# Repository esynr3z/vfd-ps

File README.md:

# Power supply for VFD

## Features

Main parts of the VFD power supply: inverting buck-boost converter on TPS54360 (supposed to use with ICs like PT6311 and etc) and filament driver on LM4871.

Inverting converter:

* Input voltage: 5V
* Output negative voltage: -15V to -30V
* Output current: 250mA @ 5V in

Filament driver:

* Input voltage: 5V
* Output voltage: 5 to 0 (dummy resistors to regulate)
* Output power: 2W @ 5V in

## Board

Schematic and pcb layout created in KiCad 6 Nightly Build (compatible with KiCad 5).

## Notes

* ```misc``` folder contains some calculation and simulation sheets for several IC to get negative voltages

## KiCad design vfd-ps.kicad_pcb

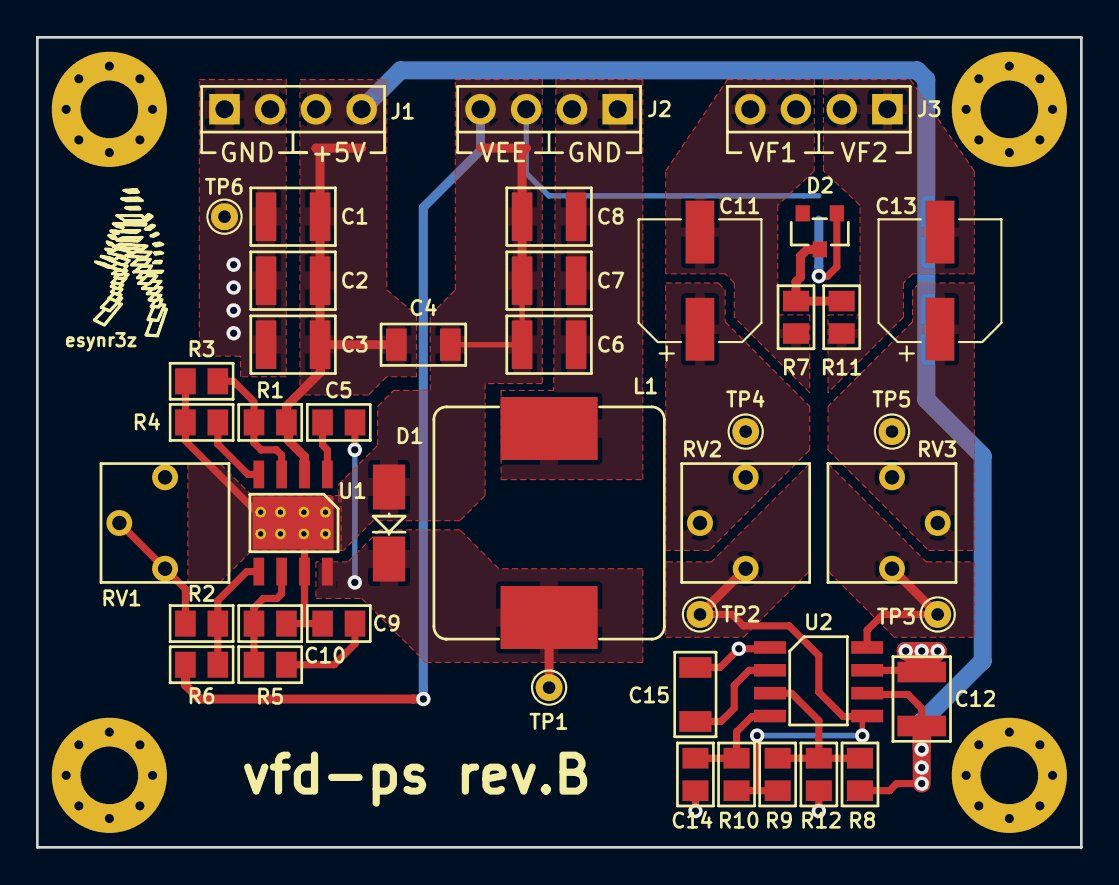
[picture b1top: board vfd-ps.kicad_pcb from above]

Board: 2 copper layers, 58.0 x 45.0 mm, 45 parts (1 on the bottom side), 22 nets.

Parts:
C1, C2, C3, C12: 22u; C_1210
C4, C15: 1u; C_1206
C5: 100n; C_0805
C6, C7, C8: 4.7u; C_1210
C9: 220n; C_0805
C10: 1.8n; C_0805
C11, C13: 22u; CP_Elec_6.3x7.7
C14: 10n; C_0805
D1: MBRA340; SMA
D2: BZX84C4V7; SOT-23
J1, J2, J3: Conn_01x04; PinHeader_1x04_P2.54mm_Vertical
JP1: SolderJumper_2_Bridged; SolderJumper-2_P1.3mm_Bridged2Bar_RoundedPad1.0x1.5mm
L1: 33u; Sumida_CDRH127
R1, R3: dnf; R_0805
R2: 36k; R_0805
R4: 220k; R_0805
R5: 6.8k; R_0805
R6, R10: 2.2k; R_0805
R7, R11: 100; R_0805
R8, R9, R12: 10k; R_0805
RV1: 50k; Bourns_3362P
RV2, RV3: 50; Bourns_3362P
TP1, TP2, TP3, TP4, TP5, TP6: TestPoint; TestPoint_THTPad_D1.5mm_Drill0.7mm
U1: TPS54360DDA; TI_SO-PowerPAD-8_ThermalVias
U2: LM4871; SOIC-8_3.9x4.9mm_P1.27mm

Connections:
+5V: C1.1, C2.1, C3.1, C4.1, C12.1, J1.3, J1.4, R1.1, R8.2, U1.2, U2.6
GND: C1.2, C2.2, C3.2, C6.1, C7.1, C8.1, C12.2, C14.2, C15.2, J1.1, J1.2, J2.1, J2.2, L1.2, R12.2, RV1.1, TP6.1, U2.1, U2.7
GNDPAD: C4.2, C6.2, C7.2, C8.2, C9.2, C10.2, D1.2, J2.3, J2.4, JP1.1, R3.2, R4.2, R6.2, U1.7, U1.9
unnamed: C5.1, U1.1
unnamed: C5.2, D1.1, L1.1, TP1.1, U1.8
unnamed: C9.1, R5.2
unnamed: C10.1, R5.1, U1.6
unnamed: C11.1, RV2.1, RV2.2, TP4.1
unnamed: C13.1, RV3.2, RV3.3, TP5.1
unnamed: C14.1, R10.1, U2.4
unnamed: C15.1, U2.2
unnamed: D2.1, JP1.2
unnamed: D2.3, R7.2, R11.1
unnamed: R1.2, R3.1, U1.3
unnamed: R2.1, RV1.2, RV1.3
unnamed: R2.2, R6.1, U1.5
unnamed: R4.1, U1.4
unnamed: R9.2, R10.2, RV2.3, TP2.1, U2.5
unnamed: R8.1, R9.1, R12.1, U2.3
unnamed: RV3.1, TP3.1, U2.8
VF1: C11.2, J3.3, J3.4, R7.1
VF2: C13.2, J3.1, J3.2, R11.2

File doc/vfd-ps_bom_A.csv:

Component,Description,Part,References,Value,Footprint,Quantity Per PCB,Datasheet,Rating
1,,Device_C,C10,1.8n,C_0805,1,~,
2,,Device_C,C5,100n,C_0805,1,~,
3,,Device_C,C14,10n,C_0805,1,~,
4,,Device_C,C4 C15,1u,C_1206,2,~,50V X7R
5,,Device_C,C9,220n,C_0805,1,~,
6,,Device_C,C1 C2 C3 C12,22u,C_1210,4,~,16V X5R
7,,Device_CP,C11 C13,22u,CP_Elec_6.3x7.7,2,~,50V
8,,Device_C,C6 C7 C8,4.7u,C_1210,3,~,50V X7R
9,,esynr3z_DiodeZener_BZX84C4V7,D2,BZX84C4V7,SOT-23,1,https://www.onsemi.com/pub/Collateral/BZX84C2V4LT1-D.PDF,
10,,esynr3z_DiodeSchottky_MBRA340,D1,MBRA340,SMA,1,https://www.onsemi.com/pub/Collateral/MBRA340T3-D.PDF,
11,,Connector_Generic_Conn_01x04,J1 J2 J3,Conn_01x04,PinHeader_1x04_P2.54mm_Vertical,3,~,
12,,Device_L_Core_Iron,L1,33u,Sumida_CDRH127,1,~,
13,,Device_R,R7 R11,100,R_0805,2,~,
14,,Device_R,R8 R9 R12,10k,R_0805,3,~,
15,,Device_R,R2,16k,R_0805,1,~,
16,,Device_R,R6,1k,R_0805,1,~,
17,,Device_R,R10,2.2k,R_0805,1,~,
18,,Device_R,R4,220k,R_0805,1,~,
19,,Device_R,R5,6.8k,R_0805,1,~,
20,,Device_R_POT_TRIM,RV1,20k,Bourns_3362P,1,~,
21,,Device_R_POT_TRIM,RV2 RV3,50,Bourns_3362P,2,~,
22,,esynr3z_AmplifierAudio_LM4871,U2,LM4871,VSSOP-8_3.0x3.0mm_P0.65mm,1,http://www.ti.com/lit/ds/symlink/lm4871.pdf,
23,,esynr3z_RegulatorSwitching_TPS54360DDA,U1,TPS54360DDA,TI_SO-PowerPAD-8_ThermalVias,1,www.ti.com/lit/ds/symlink/tps54360.pdf,





Component Groups:,24
Component Count:,38
Fitted Components:,36
Number of PCBs:,1
Total components:,36
Schematic Version:,A
Schematic Date:,
BoM Date:,Tue 25 Sep 2018 20:55:03 MSK
Schematic Source:,/home/esynr3z/MyRepos/vfd-ps/vfd-ps.sch
KiCad Version:,Eeschema 6.0.0-rc1-unknown-r13783-618182dc

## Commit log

2018-08-11 Add filament driver on ad8534
2018-08-11 ad8534-filament: add series resistor for setting up current
2018-08-11 ad8534-filament: rename voltage sources
2018-08-11 Add ncp3163 calculation worksheet
2018-08-11 Add zener to bias filament
2018-08-12 ad8534-filament: fix component nominals
2018-08-21 Add some info about vfd specs
2018-08-24 Add filament driver model on lm4871
2018-08-25 Add pulse gen to lm4871 model
2018-08-26 Rename dir with sim models, calculations and other info
2018-08-26 Add kicad project
2018-08-30 Draw first schematic
2018-09-16 Add LM2576 inverting buck-boost simulation
2018-09-17 Add TPS54360 inverting buck-boost smath calculations
2018-09-17 Update TPS54360 calculation sheet
2018-09-18 Some tweaks to TPS54360 calculations
2018-09-18 Update TPS54360 calculation
2018-09-18 Replace NCP3163 converter with TPS54360
2018-09-19 Schematic update: footprints, nominals, testpoints, etc
2018-09-19 Minor tweaks in schematic
2018-09-19 Place all components on pcb
2018-09-19 Place all references on silk layer
2018-09-20 Minor components placement tweaks
2018-09-20 Replace connectors, add testpoints, pcb rotate and align
2018-09-20 Trace buck-boost pcb part
2018-09-20 Trace all pcb nets
2018-09-21 Add image to silk
2018-09-21 Some minor silk fixes
2018-09-22 Make project portable
2018-09-22 Fix readme
2018-09-25 Update revision numbering
2018-09-25 Update docs
2018-09-26 Add gerbers
2019-10-08 Align fab layer labels
2019-10-08 Fix wrong cap polarity in fillament scheme
2019-10-08 Add fixed gerbers
2019-10-12 Change R1, R2, Rtrim values in tps54360 calculation sheet
2019-10-13 Remove all local libs and switch to submodule library
2019-10-13 Replace lm4871 footprint
2019-10-13 Align labels on silk and fab layers
2019-10-14 Revision B
2019-10-15 Fix zener pinout
